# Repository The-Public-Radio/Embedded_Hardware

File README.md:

# PR_Public_Radio
Created 2013.12.17
by Spencer Wright |
Updated by Spencer Wright 2015.01.21

## LICENSE
In the interest of collaboration and good will, the files herein are offered for public use. Just don't be a jerk about it, etc., and do let us know if we've screwed something really big up:).
The Public Radio is licensed under a Creative Commons Attribution 4.0 License. For more info, visit https://creativecommons.org/licenses/by/4.0/

## PROJECT DESCRIPTION
The Public Radio is a single channel, single speaker FM receiver. 
As a piece of hardware, it was intended to be as simple as possible. One midrange speaker mounted inside a simple enclosure, with a single switched knob which controls power and adjusts volume.

## SYNOPSIS
The Public Radio is a project which spans industrial design, embedded systems design, and firmware. The files located within this project comprise a subset of the data reqired to fully complete ThePublic Radio, though efforts are being made to completely describe the project from top to bottom.

## CREDITS
The work herein is primarily a collaboration between Spencer Wright (http://pencerw.com) and Zach Dunham (http://zachdunham.com) though much of it was adapted heavily from friendly sources. In particular, early versions of the firmware was adapted directly from Nathan Seidle et al (Sparkfun). Special thanks also goes to Todd Bailey (http://blog.narrat1ve.com/) and Andy Warner (https://github.com/andyw-lala?tab=activity)

## Board and Layout

PR90XX is a circular PCB with an OD of 70mm and a 23mm circular cutout at its center. The cutout is designed such that the radio's speaker drops partly through the PCB; its backside passes through the cutout. The antenna and trim pot are additionally mounted directly to the board and pass through the top of the lid. Two sets of two AA battery clips are mounted on the bottom side of the board to house the two AA batteries.

Early on in the project, we planned on building a custom aluminum enclosure, but decided to protoype using an off-the-shelf container - a Ball brand mason jar. The enclosure requires one custom manufactured part: a replacement lid, to which the speaker, potentiometer, and electronics mount.

## CONTAINED HEREIN
* Embedded systems design files: Namely .brd, .sch, possibly gerbers. These will remain up-to-date, so long as we can stay on our game:)
* Firmware: Arduino sketches, library files (header & source). 
* Miscellaneous tools: This currently comprises of just a shell script used to create CSVs from EAGLE exports, which generally suck. The script is okay, though.

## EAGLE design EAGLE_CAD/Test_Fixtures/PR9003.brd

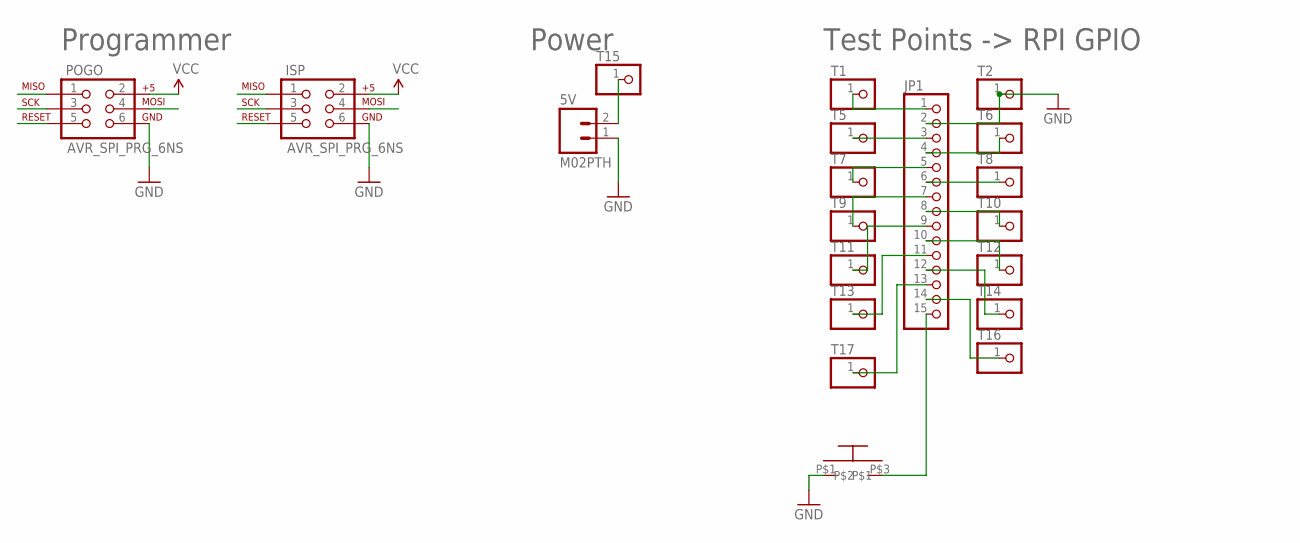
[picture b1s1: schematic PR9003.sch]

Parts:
5V: M02PTH; 1X02
ISP: AVR_SPI_PRG_6NS; 2X3-NS
JP1: PINHD-1X15; 1X15
POGO: AVR_SPI_PRG_6NS; 2X3-NS
T1, T2, T5, T6, T7, T8, T9, T10, T11, T12, T13, T14, T15, T16, T17: PINHD-1X1; 1X01
U$1: C&K_D6C_SWITCH

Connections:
GND: 5V.1, ISP.6, JP1.2, POGO.6, T2.1, U$1.P$1
MISO: ISP.1, POGO.1
MOSI: ISP.4, POGO.4
unnamed: JP1.1, T1.1
unnamed: JP1.3, T5.1
unnamed: JP1.4, T6.1
unnamed: JP1.5, T7.1
unnamed: JP1.6, T8.1
unnamed: JP1.7, T9.1
unnamed: JP1.8, T10.1
unnamed: JP1.9, T11.1
unnamed: JP1.10, T12.1
unnamed: JP1.11, T13.1
unnamed: JP1.12, T14.1
unnamed: 5V.2, T15.1
unnamed: JP1.14, T16.1
unnamed: JP1.13, T17.1
unnamed: JP1.15, U$1.P$3
RESET: ISP.5, POGO.5
SCK: ISP.3, POGO.3
VCC: ISP.2, POGO.2

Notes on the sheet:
Power
Test Points -> RPI GPIO
Programmer

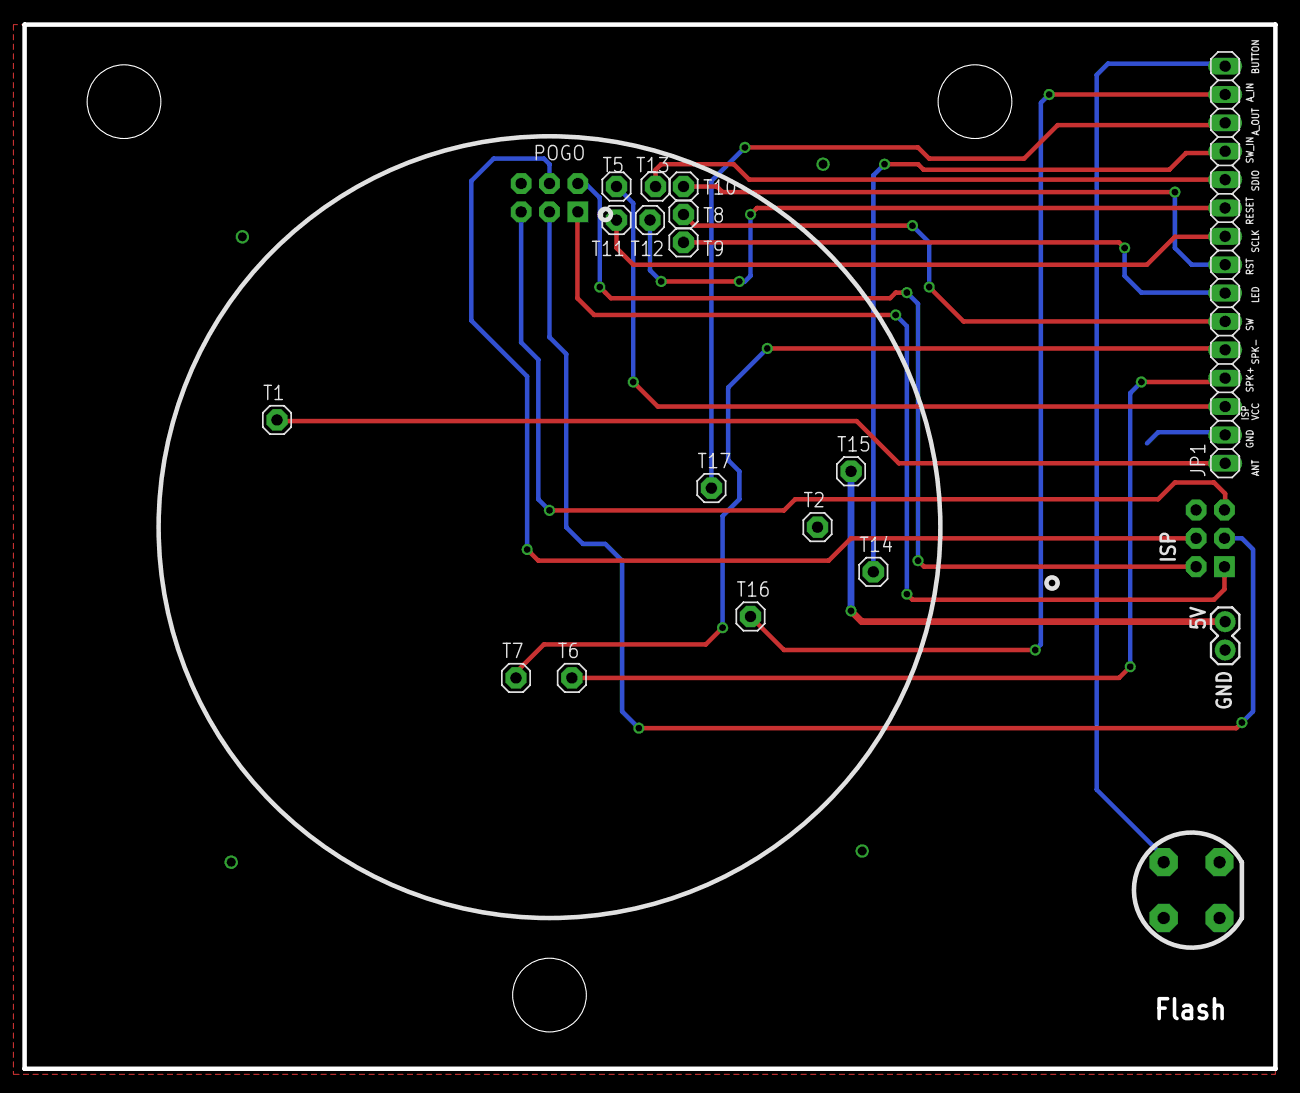
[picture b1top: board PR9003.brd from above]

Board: 2 copper layers, 112.0 x 93.5 mm, 20 parts (1 on the bottom side), 21 nets.

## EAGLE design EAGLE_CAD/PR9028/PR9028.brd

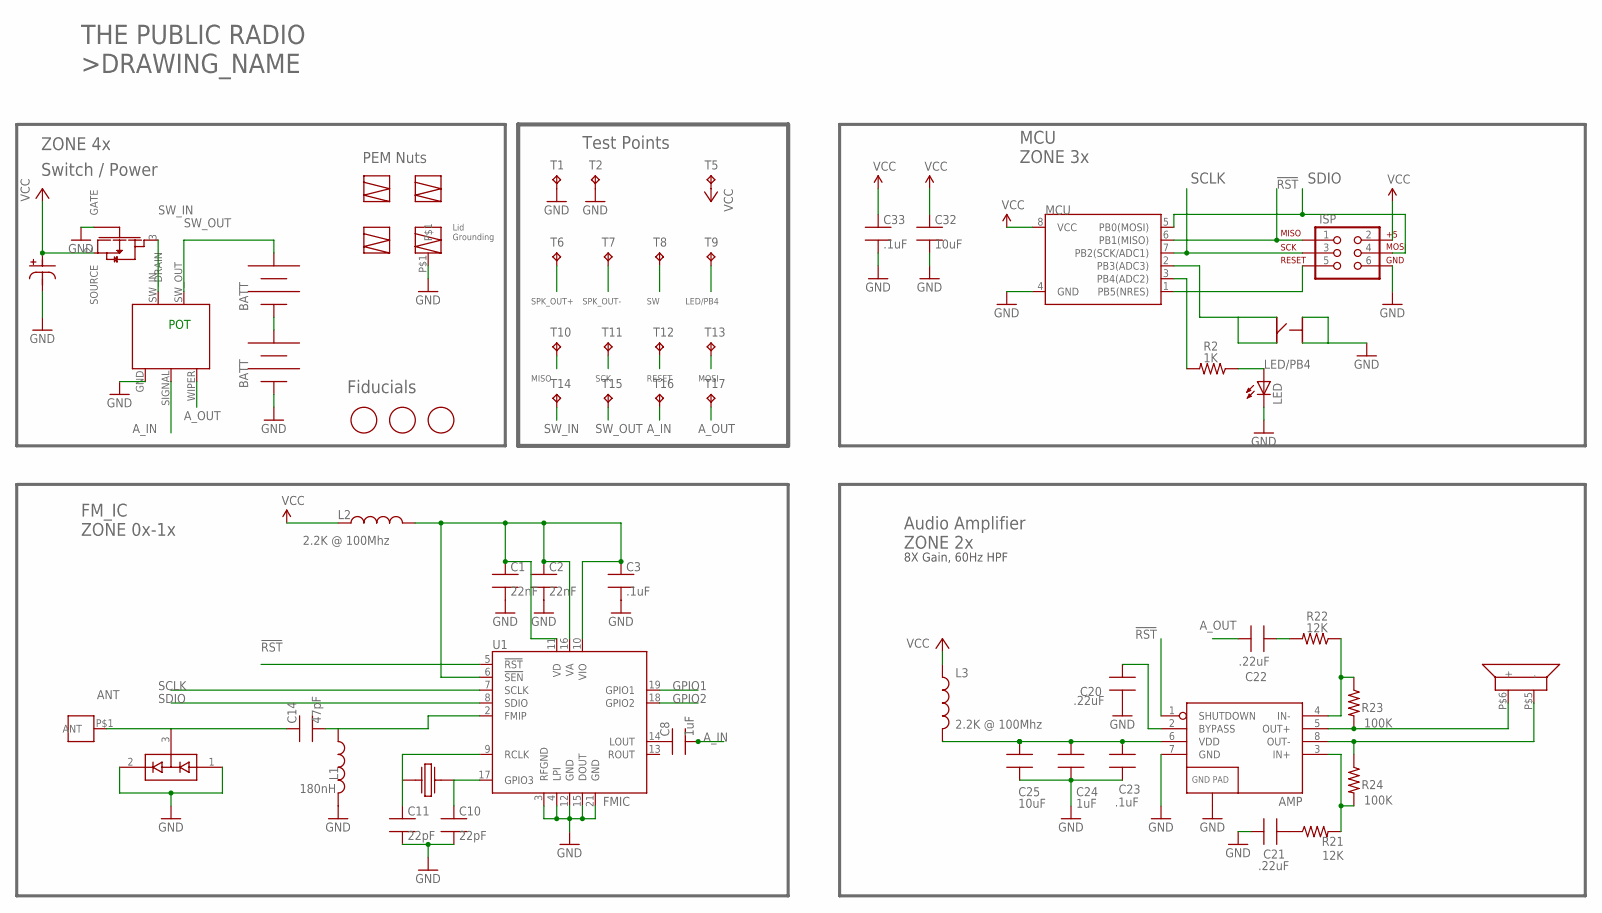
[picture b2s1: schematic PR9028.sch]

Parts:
AMP: TPA6203A1; 8-MSOP
ANT_MOUNT: PEM_M3_ANTENNA; MFG_PN Consigned
C1, C2: 22nF; 0603_CPL; VOLTAGE 16V; MFG_PN CL10B223KB8NNNC
C3, C23, C33: .1uF; 0603_CPL; VOLTAGE 16V; MFG_PN CL10B104KB8SFNC
C8, C24: 1uF; 0603_CPL; VOLTAGE 10V; MFG_PN CL10B105KP8NNNC
C10, C11: 22pF; 0603_CPL; VOLTAGE 50V; MFG_PN C1608C0G1H220J080AA
C14: 47pF; 0603_CPL; VOLTAGE 50V; MFG_PN CL10C470JB8NCNC
C20, C21, C22: .22uF; 0603_CPL; VOLTAGE 16V; MFG_PN C1608X7R1C224K080AC
C25, C32: 10uF; 0603_CPL; VOLTAGE 6.3V; MFG_PN CL10A106MQ8NNNC
C40: 220uF; NICHICON_UD_63; VOLTAGE 16V
D1: BAV99; SOT23_CPL; MFG_PN BAV99,215
FET1: AO3435; SOT23_CPL; MFG_PN AO3435
ISP: AVR_SPI_PRG_6NS; 2X3-NS; MFG_PN DNP
JP5, JP6: BK-92_MPD_AA_BATT_CLIP; BK92_AA_BATT; MFG_PN Consigned
L1: 180nH; 0805_ADAFRUIT; MFG_PN AISC-0805-R18J-T
L2, L3: 2.2K @ 100Mhz; 0603_CPL
LED: HSMC-C265_REVERSE_MOUNT_LED; HSMA-C265_REVERSE_MOUN_LED; MFG_PN HSMA-C265
MARK1, MARK2, MARK3: FIDUCIAL; FIDUCIAL_1MM
MCU: ATTINY45TINY45-20-SMT; 8-SOIC; MFG_PN ATTINY25-20SUR
R1: VOLUME_POTTAIWAN_ALPHA; RV170SF_SW_POT; MFG_PN Consigned
R2: 1K; 0603_CPL; MFG_PN RR0816P-102-D
R21, R22: 12K; 0603_CPL; MFG_PN RC0603FR-0712KL
R23, R24: 100K; 0603_CPL; MFG_PN ERJ-3EKF1003V
SPEAKER: PR2023_GROUND_UP_SPEAKER; MFG_PN Consigned
SPEAKER_PEM_1, SPEAKER_PEM_2, SPEAKER_PEM_4: PEM_M3_SPK; MFG_PN Consigned
SPEAKER_PEM_3: PEM_M3_SPK_GROUND; PEM_M3_SPK; MFG_PN Consigned
SW1: C&K_PTS645; C&K_PTS645_SMT
T1, T2, T5, T6, T7, T8, T9, T10, T11, T12, T13, T14, T15, T16, T17: TPTP20R; TP20R
U1: FMIC; SI470X_20_QFN; MFG_PN SI4702-C19-GMR
X1: ABS25XTAL; 4-SOJ

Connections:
!RST: AMP.1 (SHUTDOWN), ISP.1, MCU.6 (PB1(MISO)), T10.TP, U1.5 (!RST)
ANT: ANT_MOUNT.P$1, C14.1, D1.3 (COM)
A_IN: C8.2, R1.SIGNAL, T16.TP
A_OUT: C22.2, R1.WIPER, T17.TP
GND: AMP.7 (GND), AMP.9 (GND), C1.2, C2.2, C3.2, C10.2, C11.2, C20.1, C21.1, C23.2, C24.2, C25.2, C32.2, C33.2, C40.P$2, D1.1 (A1), D1.2 (C2), FET1.1 (GATE), ISP.6, JP6.NEG, JP6.NEG@2 (NEG), L1.2, LED.P$2 (GND), MCU.4 (GND), R1.GND, SPEAKER_PEM_3.P$1, SW1.P$1, SW1.P$2, T1.TP, T2.TP, U1.3 (RFGND), U1.4 (LPI), U1.12 (GND), U1.15 (DOUT), U1.21 (GND)
GPIO1: U1.19 (GPIO1)
GPIO2: U1.18 (GPIO2)
LED/PB4: MCU.3 (PB4(ADC2)), R2.2, T9.TP
unnamed: C11.1, U1.9 (RCLK), X1.P$1
unnamed: LED.P$1 (VCC), R2.1
unnamed: C22.1, R22.2
unnamed: AMP.6 (VDD), C23.1, C24.1, C25.1, L3.2
unnamed: AMP.3 (IN+), R21.2, R24.2
unnamed: C1.1, C2.1, C3.1, L2.2, U1.6 (!SEN), U1.10 (VIO), U1.11 (VD), U1.16 (VA)
unnamed: C8.1, U1.14 (LOUT)
unnamed: C10.1, U1.17 (GPIO3), X1.P$4
unnamed: AMP.2 (BYPASS), C20.2
unnamed: JP5.NEG, JP5.NEG@2 (NEG), JP6.POS, JP6.POS@2 (POS)
unnamed: AMP.4 (IN-), R22.1, R23.1
unnamed: C14.2, L1.1, U1.2 (FMIP)
unnamed: C21.2, R21.1
RESET: ISP.5, MCU.1 (PB5(NRES)), T12.TP
SCLK: ISP.3, MCU.7 (PB2(SCK/ADC1)), T11.TP, U1.7 (SCLK)
SDIO: ISP.4, MCU.5 (PB0(MOSI)), T13.TP, U1.8 (SDIO)
SPK_OUT+: AMP.5 (OUT+), R23.2, SPEAKER.P$6 (+), T6.TP
SPK_OUT-: AMP.8 (OUT-), R24.1, SPEAKER.P$5 (-), T7.TP
SW: MCU.2 (PB3(ADC3)), SW1.P$3, SW1.P$4, T8.TP
SW_IN: FET1.3 (DRAIN), R1.SW_IN, T14.TP
SW_OUT: JP5.POS, JP5.POS@2 (POS), R1.SW_OUT, T15.TP
VCC: C32.1, C33.1, C40.P$1, FET1.2 (SOURCE), ISP.2, L2.1, L3.1, MCU.8 (VCC), T5.TP

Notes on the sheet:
POT
FM_IC ZONE 0x-1x
Switch / Power
Lid Grounding
Audio Amplifier ZONE 2x
MCU ZONE 3x
THE PUBLIC RADIO >DRAWING_NAME
Fiducials
Test Points
MISO
SCK
RESET
MOSI
8X Gain, 60Hz HPF
ZONE 4x
PEM Nuts

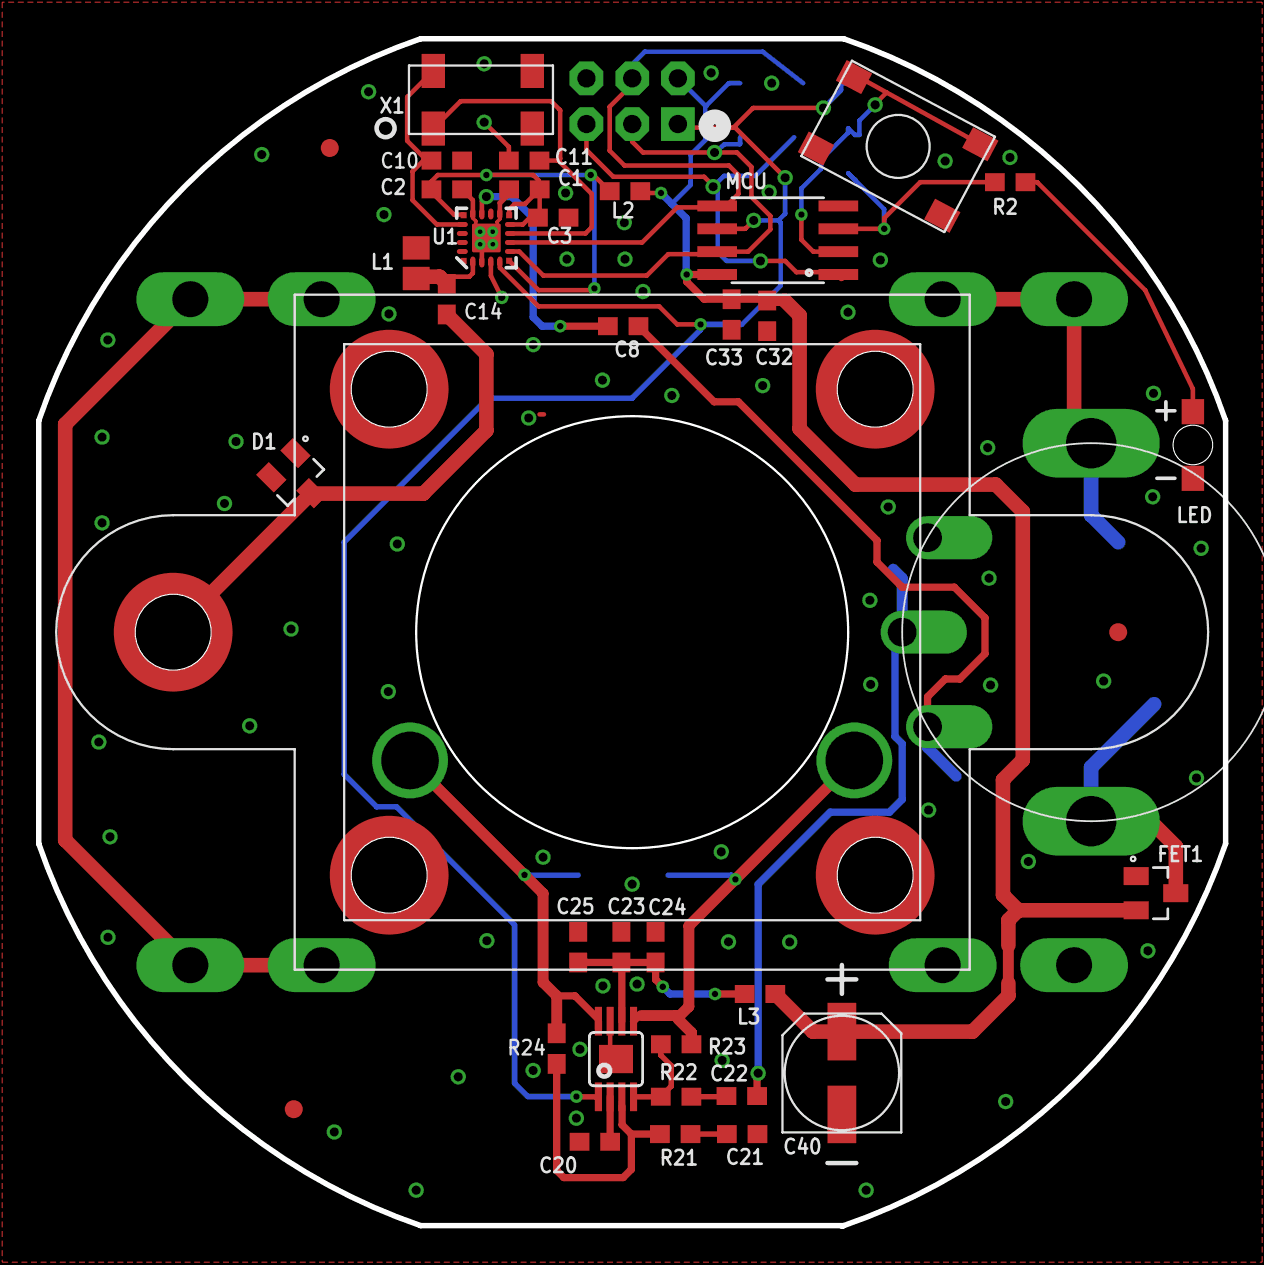
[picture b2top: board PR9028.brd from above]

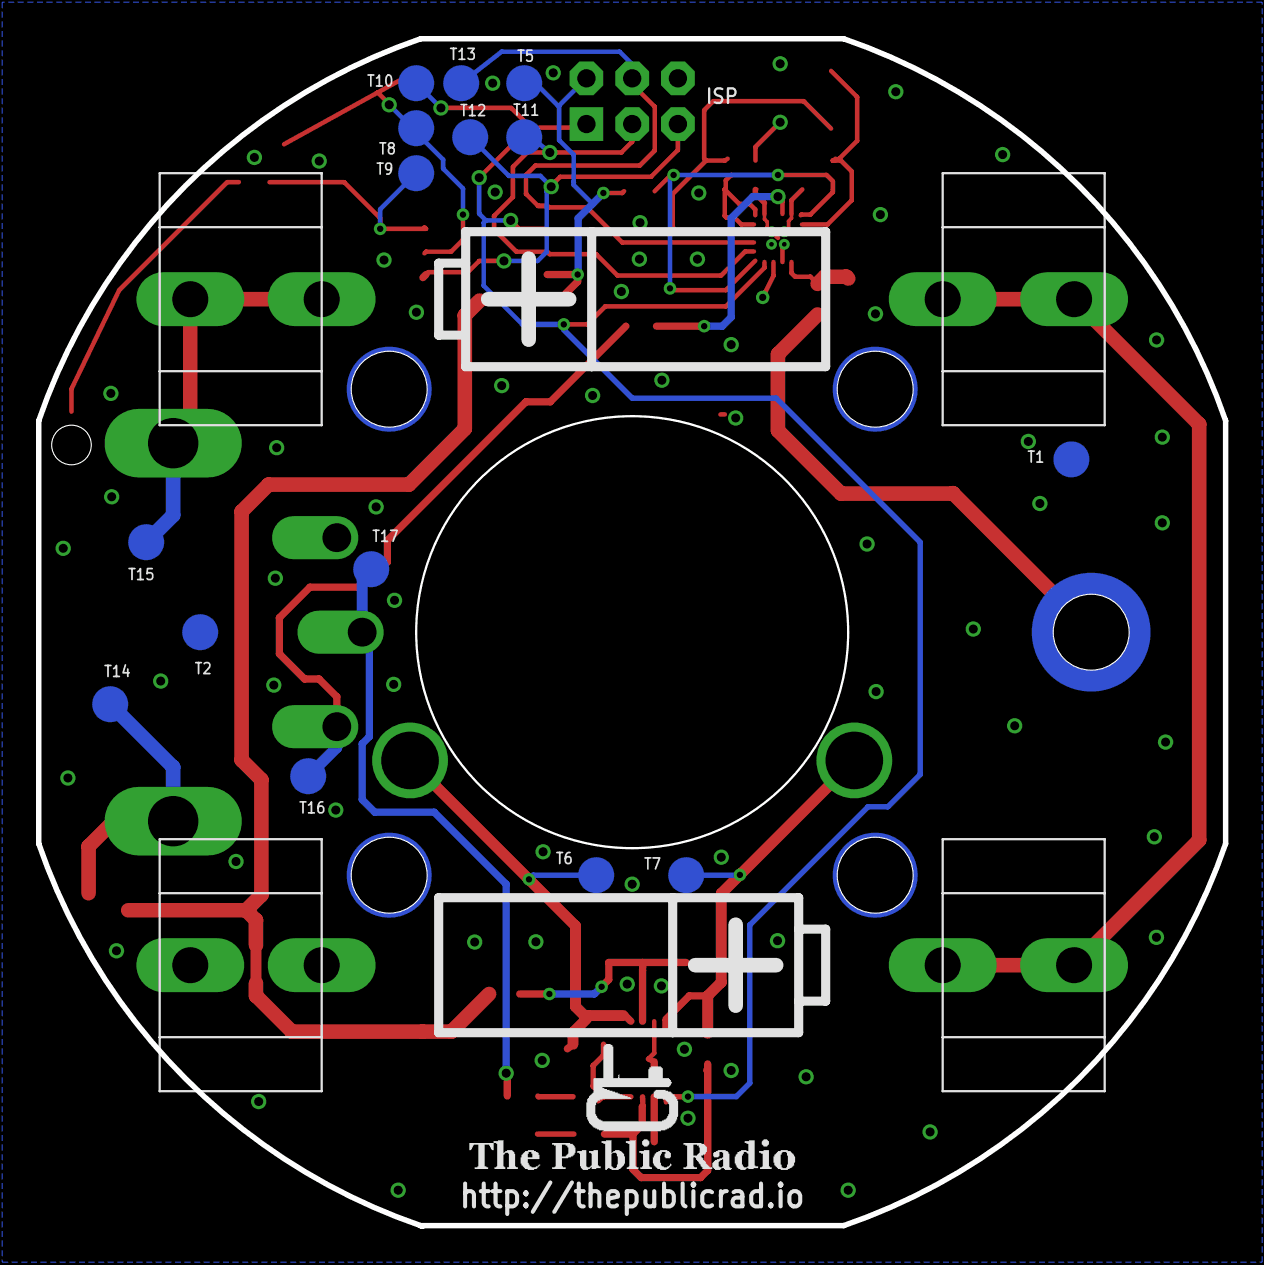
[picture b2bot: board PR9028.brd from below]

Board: 2 copper layers, 65.9 x 65.9 mm, 61 parts (19 on the bottom side), 28 nets.

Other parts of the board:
U$2: PR_LOGO_2.0

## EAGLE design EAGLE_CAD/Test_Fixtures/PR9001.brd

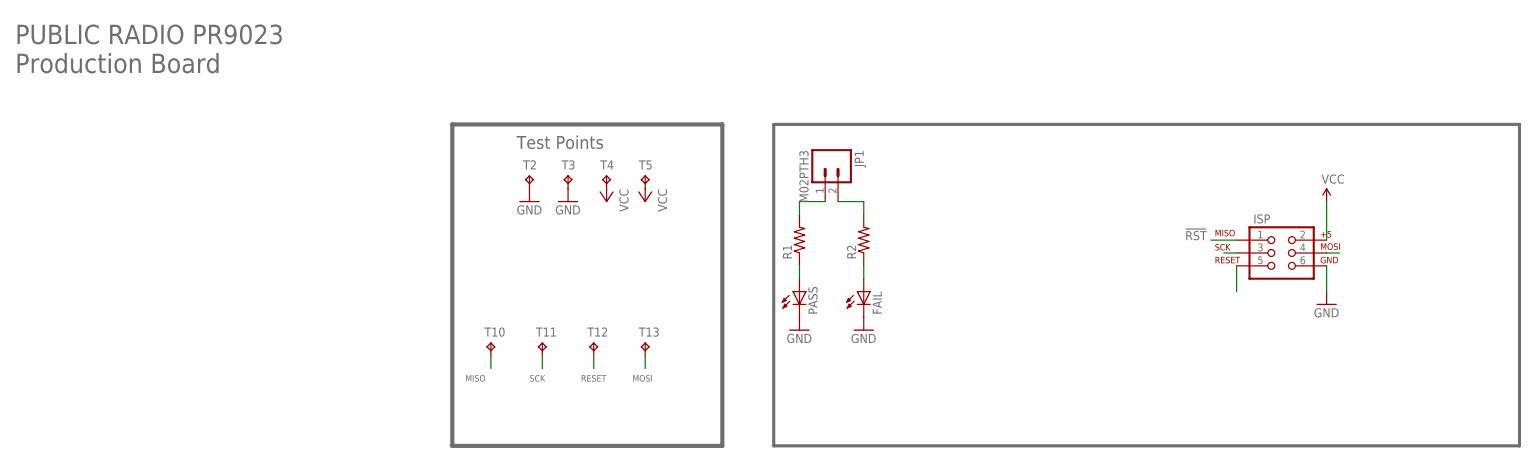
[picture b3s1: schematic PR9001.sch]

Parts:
FAIL: LED5MM
ISP: AVR_SPI_PRG_6NS; 2X3-NS
JP1: M02PTH3; 1X02_LONGPADS
PASS: LED5MM
R1, R2: RESISTORPTH-1/4W-VERT; AXIAL-0.1
T2, T3, T4, T5, T10, T11, T12, T13: PR9001_TESTPOINT

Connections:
!RST: ISP.1, T10.P$1
GND: FAIL.K (C), ISP.6, PASS.K (C), T2.P$1, T3.P$1
unnamed: JP1.2, R2.P$2 (2)
unnamed: PASS.A, R1.P$1 (1)
unnamed: JP1.1, R1.P$2 (2)
unnamed: FAIL.A, R2.P$1 (1)
RESET: ISP.5, T12.P$1
SCLK: ISP.3, T11.P$1
SDIO: ISP.4, T13.P$1
VCC: ISP.2, T4.P$1, T5.P$1

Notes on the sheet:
PUBLIC RADIO PR9023 Production Board
Test Points
MISO
SCK
RESET
MOSI

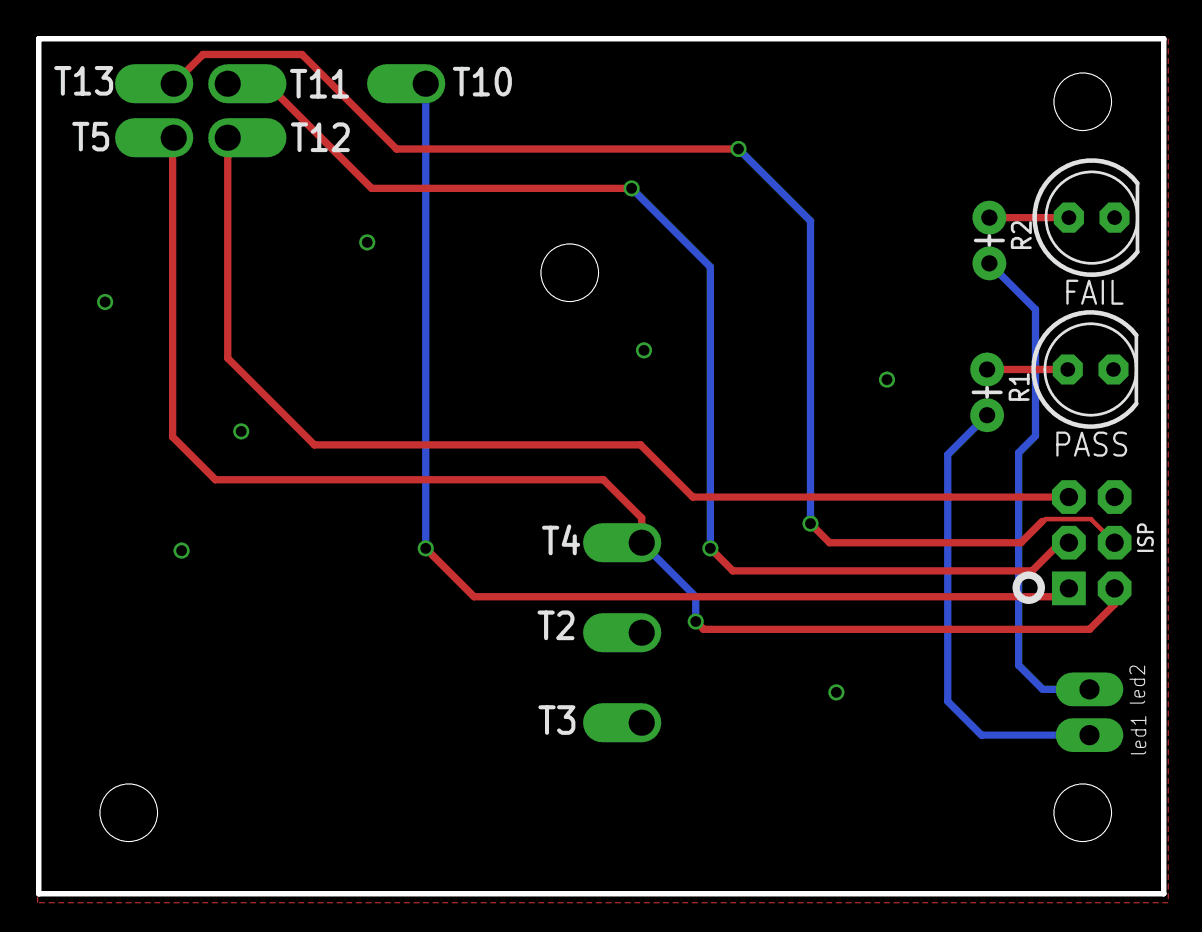
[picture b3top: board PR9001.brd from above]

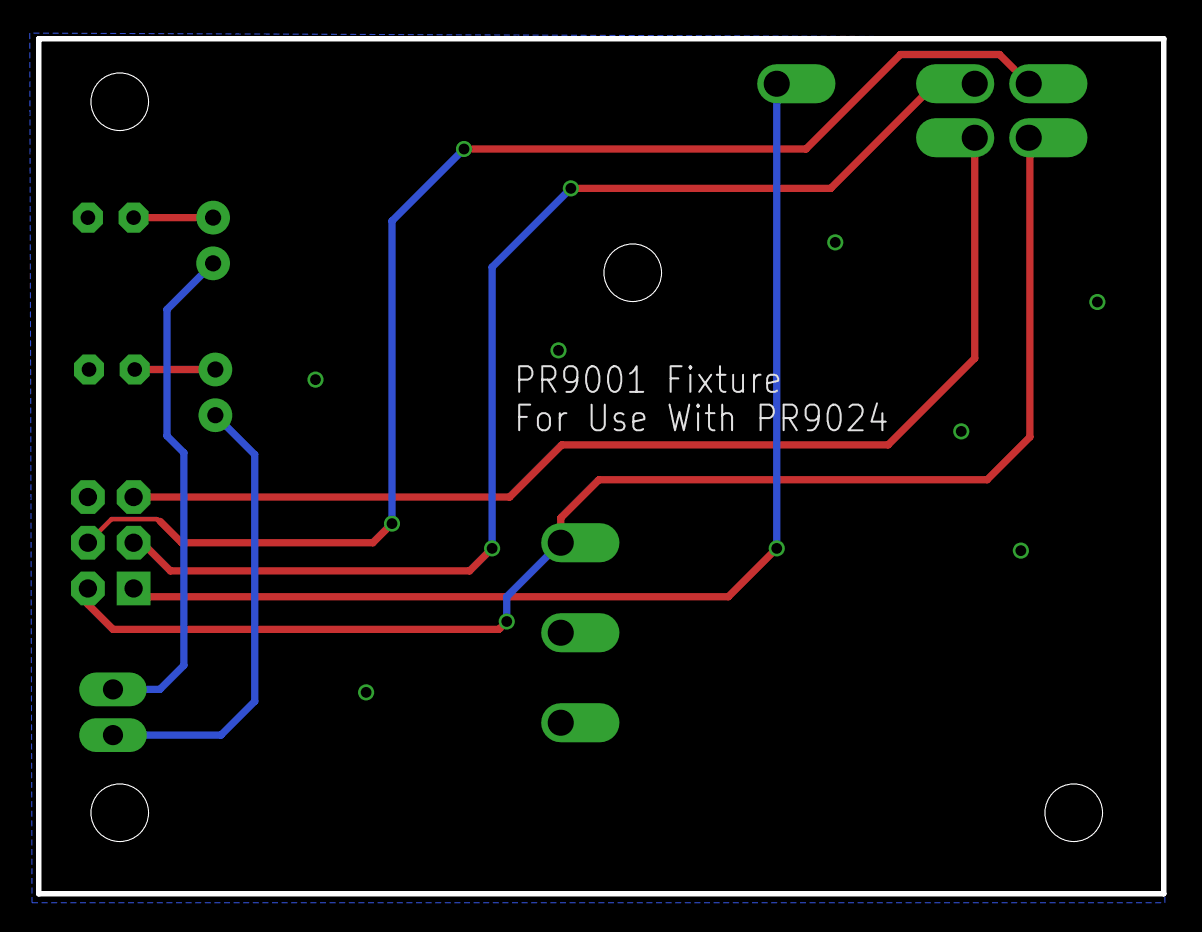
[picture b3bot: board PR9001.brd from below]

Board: 2 copper layers, 62.5 x 47.5 mm, 14 parts (9 on the bottom side), 10 nets.

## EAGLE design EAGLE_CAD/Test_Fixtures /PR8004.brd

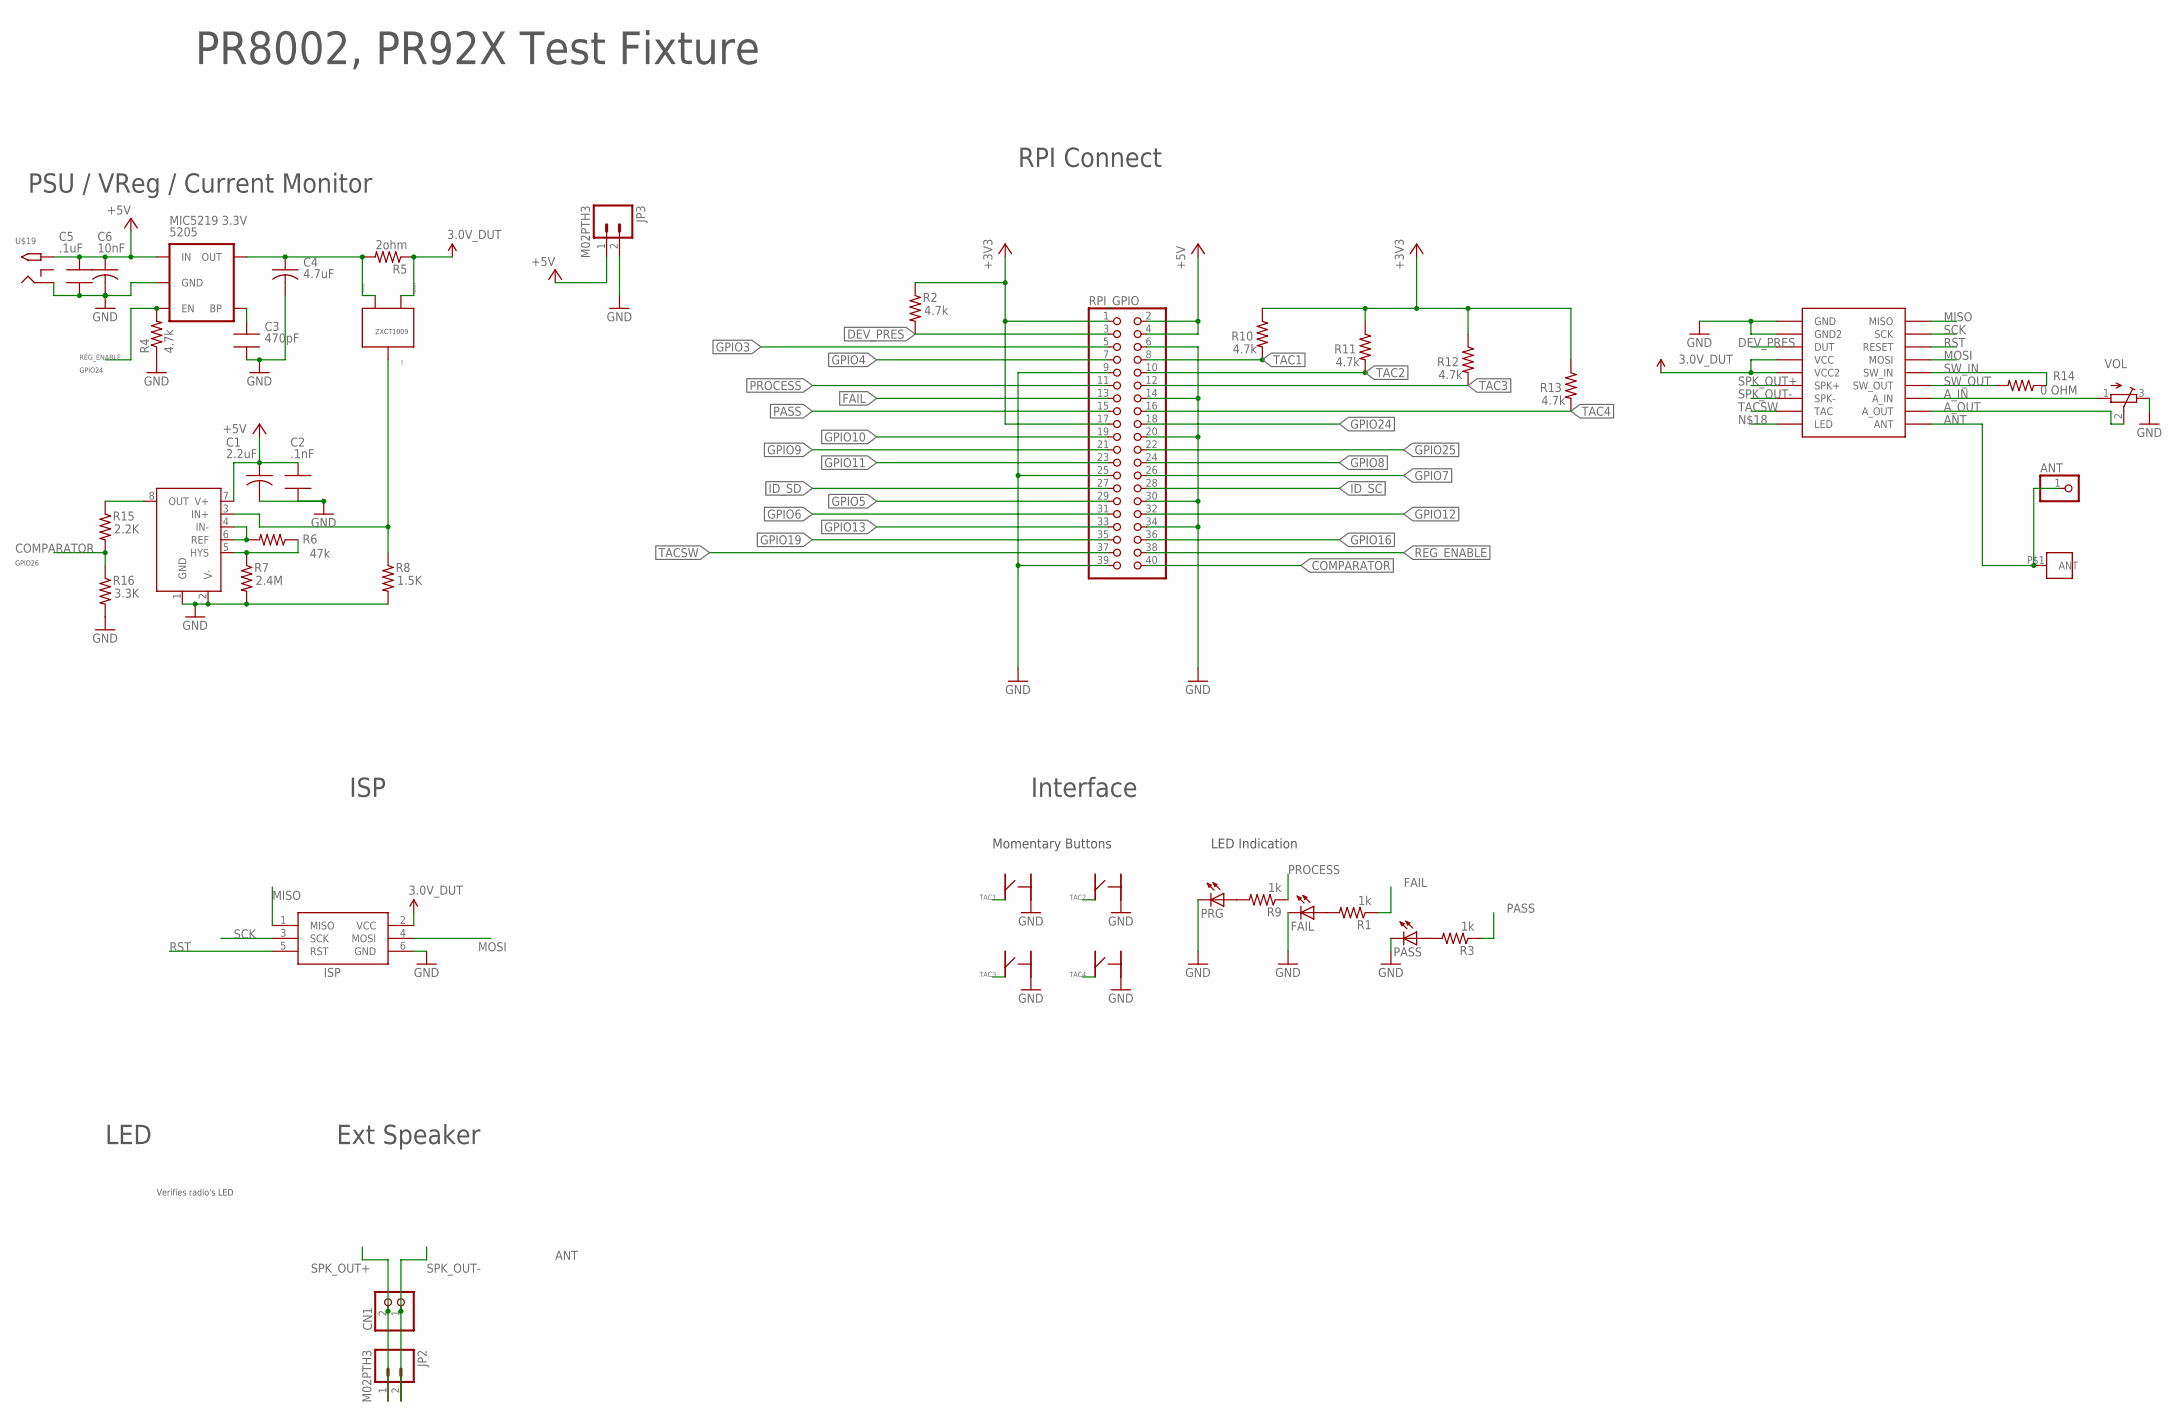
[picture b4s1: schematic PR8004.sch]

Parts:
5205: MIC5219 3.3V; SOT23-5
ANT: PINHD-1X1; 1X01
C1: 2.2uF; C0805
C2: .1nF; 0805_ADAFRUIT
C3: 470pF; 0805_ADAFRUIT
C4: 4.7uF; C0805
C5: .1uF; 0805_ADAFRUIT
C6: 10nF; C0805
CN1: JST_2PIN-SMT-RA; JST-B2B-PH-SM4-TB
FAIL: LEDCHIP-LED0805; CHIP-LED0805
ISP: AVRISP-6; AVRISP
J1: M3_SCREW_POST; M3_BOLT_HOLE
JP2, JP3: M02PTH3; 1X02_LONGPADS
PASS: LEDCHIP-LED0805; CHIP-LED0805
PRG: LEDCHIP-LED0805; CHIP-LED0805
R1, R3, R9: 1k; 0805_ADAFRUIT
R2, R4, R10, R11, R12, R13: 4.7k; 0805_ADAFRUIT
R5: 2ohm; 0805_ADAFRUIT
R6: 47k; 0805_ADAFRUIT
R7: 2.4M; 0805_ADAFRUIT
R8: 1.5K; 0805_ADAFRUIT
R14: 0 OHM; 0805_ADAFRUIT
R15: 2.2K; 0805_ADAFRUIT
R16: 3.3K; 0805_ADAFRUIT
RPI_GPIO: PINHD-2X20; 2X20
TSM931: TSM931; MSOP8
U$19: 2.1MMJACKTHM; PJ-102A
U$20, U$22, U$23, U$24: C&K_PTS645; C&K_PTS645_SMT
U$26: PR9020_TESTPOINTS
VOL: TRIMPOTTC33X; TC33X
ZXCT: ZXCT1009; SOT23

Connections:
3.3V: ISP.2 (VCC), R5.1, U$26.P$4 (VCC), U$26.P$5 (VCC2), ZXCT.1 (VSENSE+)
+3V3: R2.1, R10.1, R11.1, R12.1, R13.1, RPI_GPIO.1, RPI_GPIO.17
+5V: 5205.1 (IN), C1.1, C2.1, C5.1, C6.1, JP3.1, RPI_GPIO.2, RPI_GPIO.4, TSM931.7 (V+), U$19.TIP
ANT: ANT.1, J1.P$1, U$26.P$18 (ANT)
A_IN: U$26.P$16 (A_IN), VOL.1 (A)
A_OUT: U$26.P$17 (A_OUT), VOL.2 (S)
COMPARATOR: R15.2, R16.1, RPI_GPIO.40
DEV_PRES: R2.2, RPI_GPIO.3, U$26.P$3 (DUT)
FAIL: R1.1, RPI_GPIO.13
GND: 5205.2 (GND), C1.2, C2.2, C3.2, C4.2, C5.2, C6.2, FAIL.C, ISP.6 (GND), JP3.2, PASS.C, PRG.C, R4.1, R7.2, R8.2, R16.2, RPI_GPIO.6, RPI_GPIO.9, RPI_GPIO.14, RPI_GPIO.20, RPI_GPIO.25, RPI_GPIO.30, RPI_GPIO.34, RPI_GPIO.39, TSM931.1 (GND), TSM931.2 (V-), U$19.RING, U$20.P$2, U$22.P$2, U$23.P$2, U$24.P$2, U$26.P$1 (GND), U$26.P$2 (GND2), VOL.3 (E)
GPIO3: RPI_GPIO.5
GPIO4: RPI_GPIO.7
GPIO5: RPI_GPIO.29
GPIO6: RPI_GPIO.31
GPIO7: RPI_GPIO.26
GPIO8: RPI_GPIO.24
GPIO9: RPI_GPIO.21
GPIO10: RPI_GPIO.19
GPIO11: RPI_GPIO.23
GPIO12: RPI_GPIO.32
GPIO13: RPI_GPIO.33
GPIO16: RPI_GPIO.36
GPIO19: RPI_GPIO.35
GPIO24: RPI_GPIO.18
GPIO25: RPI_GPIO.22
ID_SC: RPI_GPIO.28
ID_SD: RPI_GPIO.27
MISO: ISP.1 (MISO), U$26.P$10 (MISO)
MOSI: ISP.4 (MOSI), U$26.P$13 (MOSI)
unnamed: R6.2, TSM931.4 (IN-), TSM931.6 (REF)
unnamed: PRG.A, R9.2
unnamed: FAIL.A, R1.2
unnamed: PASS.A, R3.2
unnamed: R15.1, TSM931.8 (OUT)
unnamed: R8.1, TSM931.3 (IN+), ZXCT.3 (IOUT)
unnamed: 5205.4 (BP), C3.1
unnamed: 5205.5 (OUT), C4.1, R5.2, ZXCT.2 (VSENSE-)
unnamed: R6.1, R7.1, TSM931.5 (HYS)
PASS: R3.1, RPI_GPIO.15
PROCESS: R9.1, RPI_GPIO.11
REG_ENABLE: 5205.3 (EN), R4.2, RPI_GPIO.38
RST: ISP.5 (RST), U$26.P$12 (RESET)
SCK: ISP.3 (SCK), U$26.P$11 (SCK)
SPK_OUT+: CN1.2 (1), JP2.1, U$26.P$6 (SPK+)
SPK_OUT-: CN1.1 (2), JP2.2, U$26.P$7 (SPK-)
SW_IN: R14.2, U$26.P$14 (SW_IN)
SW_OUT: R14.1, U$26.P$15 (SW_OUT)
TAC1: R10.2, RPI_GPIO.8, U$20.P$4
TAC2: R11.2, RPI_GPIO.10, U$23.P$4
TAC3: R12.2, RPI_GPIO.12, U$22.P$4
TAC4: R13.2, RPI_GPIO.16, U$24.P$4
TACSW: RPI_GPIO.37, U$26.P$8 (TAC)

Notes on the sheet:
Ext Speaker
LED
ISP
PSU / VReg / Current Monitor
RPI Connect
PR8002, PR92X Test Fixture
Verifies radio's LED
Interface
GPIO24
GPIO26
ZXCT1009
Momentary Buttons
LED Indication

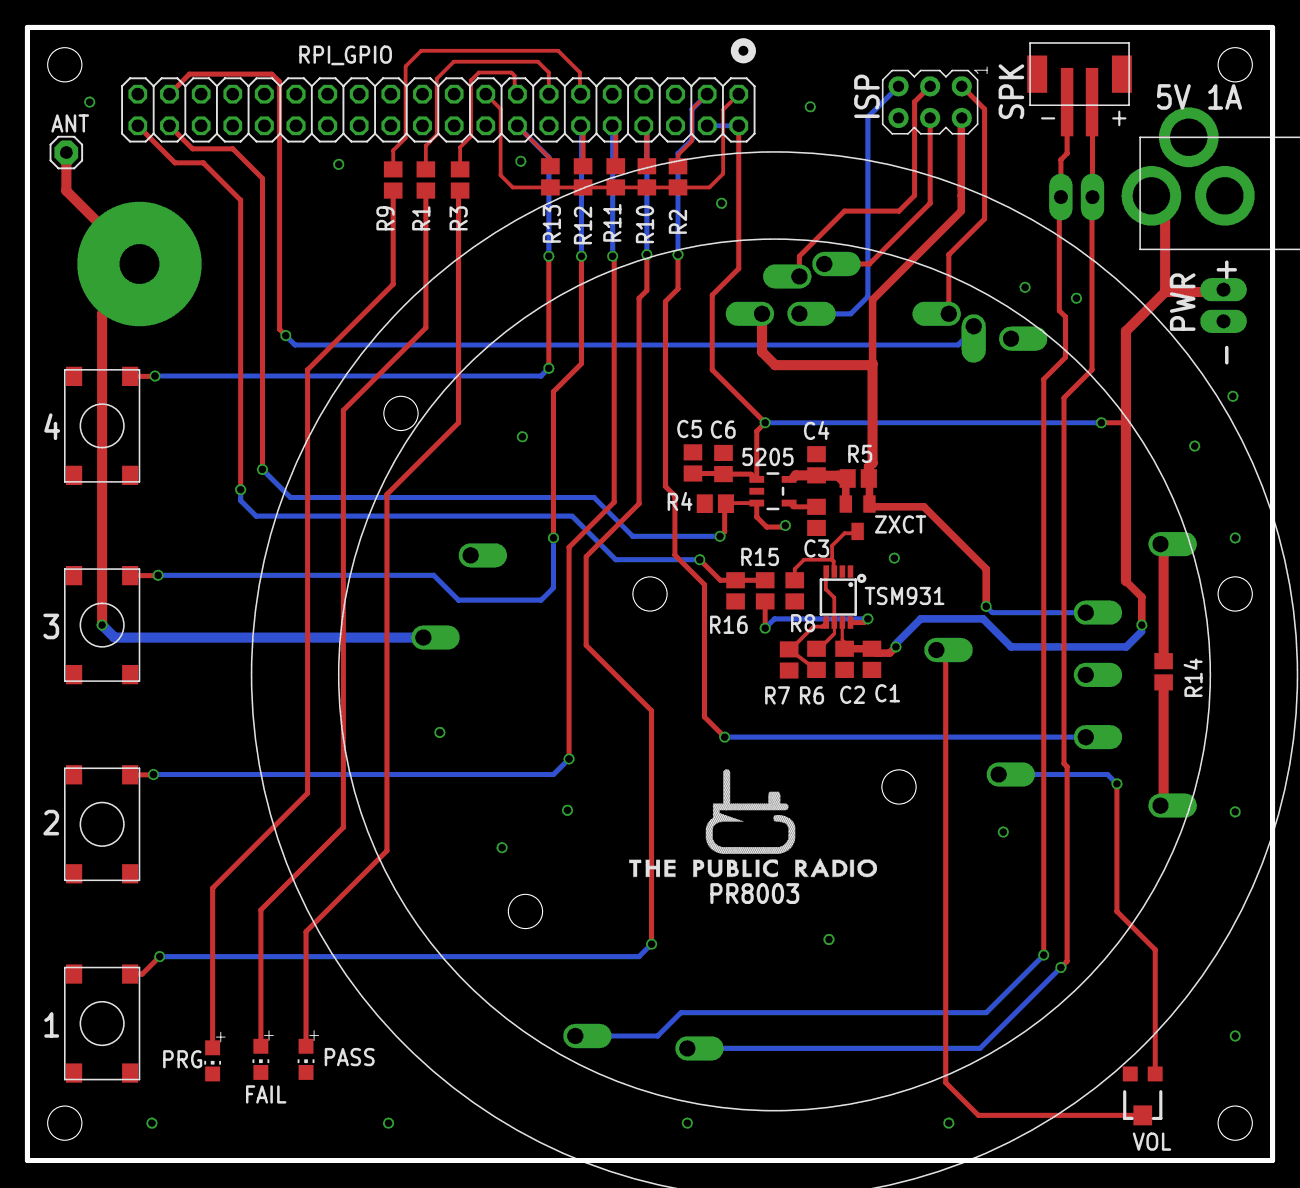
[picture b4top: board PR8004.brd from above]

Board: 2 copper layers, 100.0 x 91.0 mm, 43 parts (0 on the bottom side), 35 nets.

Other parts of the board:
U$1: PR_LOGO

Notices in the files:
parts and their libraries:
SparkFun-Aesthetics: Licensing: CC v3.0 Share-Alike You are welcome to use this library for commercial purposes.
SparkFun-PowerIC: Licensing: Creative Commons ShareAlike 4.0 International - https://creativecommons.org/licenses/by-sa/4.0
